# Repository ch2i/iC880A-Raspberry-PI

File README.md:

# Raspberry PI iC880A and LinkLab Lora Gateway Shield

At the begining this shield has been created to help wiring between Raspberry PI and ISMT [iC880A][10] LoraWan concentrator Gateway (SPI version) and to be able to put the whole thing into a outdoor enclosure such as this [one][15].

Then I decided to add some funky stuff like:

**New in V1.2** (tested, working fine)

 - Added push button on GPIO19 to be able to shutdown PI Locally (if you don't use RFM95 with IRQ) 
 - Reversed DHT connector [#4][4]
 - Added FTDI connector to be able to take hand on PI console when in enclosure (lost network or whatever, no more need to get all off the enclosure and connect HDMI cable to see what's going on)
 - Added footprint for excellent Murata OKI-78SR-5 DC/DC 5V
 - Fixed Mini Voltmeter Holes Spacing

**Still V1.1** 

- Footprint for [iC880a][10] ISMT LoraWan concentrator (main goal)
- ~~Can be also used between LinkLabs [board][11] and Raspi~~
- I2C and Grove connectors to be able to add internal/external sensors such as BME280, SI7021 or HTU21D
- Footprint for DC/DC step down if you want to do some simple [POE splitter][16] to power the whole thing thru a network cable or any power 
- Footprint for a simple Lora module such as RFM95 that can be used a Single Channel Gateway or also act as a Lora Node
- Power with DC Barrel connector and terminal block
- Four visual GPIO Led
- Footprint for DHT1x Temperature/Humidity sensors
- Easy to build and solder, 0805 or PTH components
- Holes to fix board on enclosure or other support

# Detailed Description

No specific documentation for now, it's just a kind of wiring helper, please see Gateway section on [TTN Wiki][13] and also on [TTN Forums][14] for more information on these gateways.

You can power the board with 5V going to Raspberry PI USB power directly, in this case use a descent power supply.
You can also use "basic" POE with injector and splitter, this is what I do to oustide (I inject 12V) and use the DC Barrel, in this case I put D4 and a DC/DC Step down calibrated to 5V (**do calibration before beforre pluging any boards/devices because default DC/DC output can be over 5V can fry all your boards**)

If you need to use sensors you can check out these [examples][12], they're just awesome, I'll post examples as soon as I get all working.

If you use linklabs board you can use these [version][2] of packet_forwarder, it has been modified to drive LED of linklabs boards and PPS modem line.

# Installation

No specific documentation for now, it's just a kind of wiring helper, please see Gateway section on [TTN Wiki][13] and Installation is quite easy but as the plate need to go over RPI network and USB connector, you need to use a 2x20 Raspberry PI connector such as [this one][25] form adafruit. You can also find some on ebay.

See generic SX1031 Lora Gateway setup for software [installation](https://github.com/ch2i/LoraGW-Setup)

# Schematic

# Boards 

**Top side**

**Bottom side**

You can order the PCB of this board on my [tindie store](https://www.tindie.com/products/hallard/ic880a-lora-concentrator-shield-raspberry-pi/) located in EU or at [PCBs.io][3] (not sure PCBs.io still alive). Don't worry they still have a bug with top/bottom thumbails view but final boards are okay
PCBs.io give me some reward when you order my designed boards from their site. This is pretty good, because I can use these rewards to create and design new boards and order boards for a discounted price, so if you don't care about PCB manufacturer please use PCBs.io.

## Assembled boards into nice enclosure with sensors

Sensors values en Cayenne (see [installer][26] readme for setup)

## Bill Of Material

Nothing fancy, all components are 0805 and/or PTH and can be ordered almost anywhere (digikey, mouser, radiospare, ...). 
use only what you need dependings on what you want to do. 

- ~~Adjustable DC/DC step down like this [one][18] or this [one][19]~~
- Fixed 5V DC/DC step down like this 3A [one][27] or this 1.5A [one][28] or excellent Murata [OKI-78SR-5][44]
- LED for 4 GPIO (4/23/18/24) are 3mm PTH or 0805, color of your choice
- If you use RFM95, diode for DIO0/DIO1/DIO2 (if you want to use interrupts) are 1N4148 PTH or SOD123
- POE Splitter such as [these][16] and POE injector as this [one][17]
- Terminal blocks are 5MM spacing
- D3 is 1N400x (1N4001, 1N4007, ..) whatever you have, PTH or DO214
- DC/Barell power jack 
- Grove connector and others at [seeedstudio][20]
- ~~Some PI connector with [long pins][21] for pluging this board and Linklabs one~~
- Some 2X20 pins [PI connector][29] for pluging this board  
- Antenna [UFL][22] with [IPEX][23] cable or [SMA][24] if using Lora Module
- Small Enclosure 125x125mm 75mm Height [#1][40] or [#2][41]
- optional [Outdoor protection sleeve][42] for SI7021/HTU21D
- optional [Breakout][43] for enclosure temperature monitoring BME280
- optional tactile switch like this [one][46] or for external on enclosure this [one][47] (connect button LED to Heatbeat LED (GPIO4)
- optional digital [voltmeter][48] to display input voltage
- 2 x [M4 Hex Brass Spacer Standoff][44] to fix board on enclosure, (higher give you more space below to put POE splitter for example) 25mm to 35mm is fine

# License

This work is licensed under a [Creative Commons Attribution-NonCommercial 4.0 International License](http://creativecommons.org/licenses/by-nc/4.0/)    
If you want to do commercial stuff with this project, please contact [CH2i company](https://www.ch2i.eu/en#support) so we can organize an simple agreement.

# Misc

See news and other projects on my [blog][1] 
 
[1]: https://hallard.me
[2]: https://github.com/ch2i/packet_forwarder
[3]: https://PCBs.io/share/rmVdD
[4]: https://github.com/ch2i/iC880A-Raspberry-PI/issues/4

[10]: http://webshop.imst.de/ic880a-spi-lorawan-concentrator-868mhz.html
[11]: http://forum.thethingsnetwork.org/t/raspberry-pi-lorawan-gateway-board/1071
[12]: https://github.com/leon-anavi/rpi-examples
[13]: https://staging.thethingsnetwork.org/wiki/Hardware/Gateways/Overview
[14]: http://forum.thethingsnetwork.org/c/gateways
[15]: https://www.aerial.net/shop/product_info.php?products_id=1102
[16]: https://www.aerial.net/shop/index.php?cPath=22_124
[17]: http://wiki.dragino.com/index.php?title=PoE_Injector
[18]: http://www.ebay.com/itm/2-PCS-MP1584EN-Step-down-Power-DC-DC-3A-Adjustable-Ultra-LM2596-Step-down-Module-/301798394307
[19]: http://www.ebay.com/itm/1x-Tiny-4-5-28V-3A-DC-DC-Buck-Converter-Step-down-Power-Regulator-MP1584EN-/141524007951
[20]: http://www.seeedstudio.com/depot/index.php?main_page=opl_info&opl_id=4
[21]: http://www.ebay.com/itm/170578495165
[22]: http://www.ebay.com/itm/351690376555
[23]: http://www.ebay.com/itm/351738196013
[24]: http://www.ebay.com/itm/371534934746

[25]: https://www.adafruit.com/products/1979
[26]: https://github.com/ch2i/ic880a-gateway/tree/ch2i-rpi-shield

[27]: http://www.ebay.com/itm/121929386506?var=420920026758
[28]: http://www.ebay.com/itm/371348168950
[29]: http://www.ebay.com/itm/351588181858

[30]: https://github.com/ch2i/packet_forwarder/blob/master/poly_pkt_fwd/readme.md

[40]: http://www.ebay.com/itm/262500056078
[41]: http://www.aliexpress.com/item/Free-Shipping-Good-Quality-ABS-Material-Transparent-Cover-IP66-Waterproof-Electrical-Switch-Box-125-125-75mm/32522255056.html
[42]: http://www.aliexpress.com/item/Temperature-and-humidity-Protective-sleeve-Accessories-PCB-for-SHT20-SHT21-SHT25/32695663191.html?spm=2114.13010208.99999999.264.dgLxek
[43]: http://www.ebay.com/itm/401000227934
[44]: http://www.ebay.com/itm/182181715511?var=483966356069
[45]: http://www2.mouser.com/ProductDetail/Murata-Power-Solutions/OKI-78SR-5-15-W36H-C/?qs=sGAEpiMZZMt6Q9lZSPl3Rb6uckMsyldgZf%2f4GdkUxM8%3d
[46]: http://www.ebay.com/itm/391462862706
[47]: http://www.ebay.com/itm/232153789354?var=531358445664
[48]: http://www.ebay.com/itm/301856945402

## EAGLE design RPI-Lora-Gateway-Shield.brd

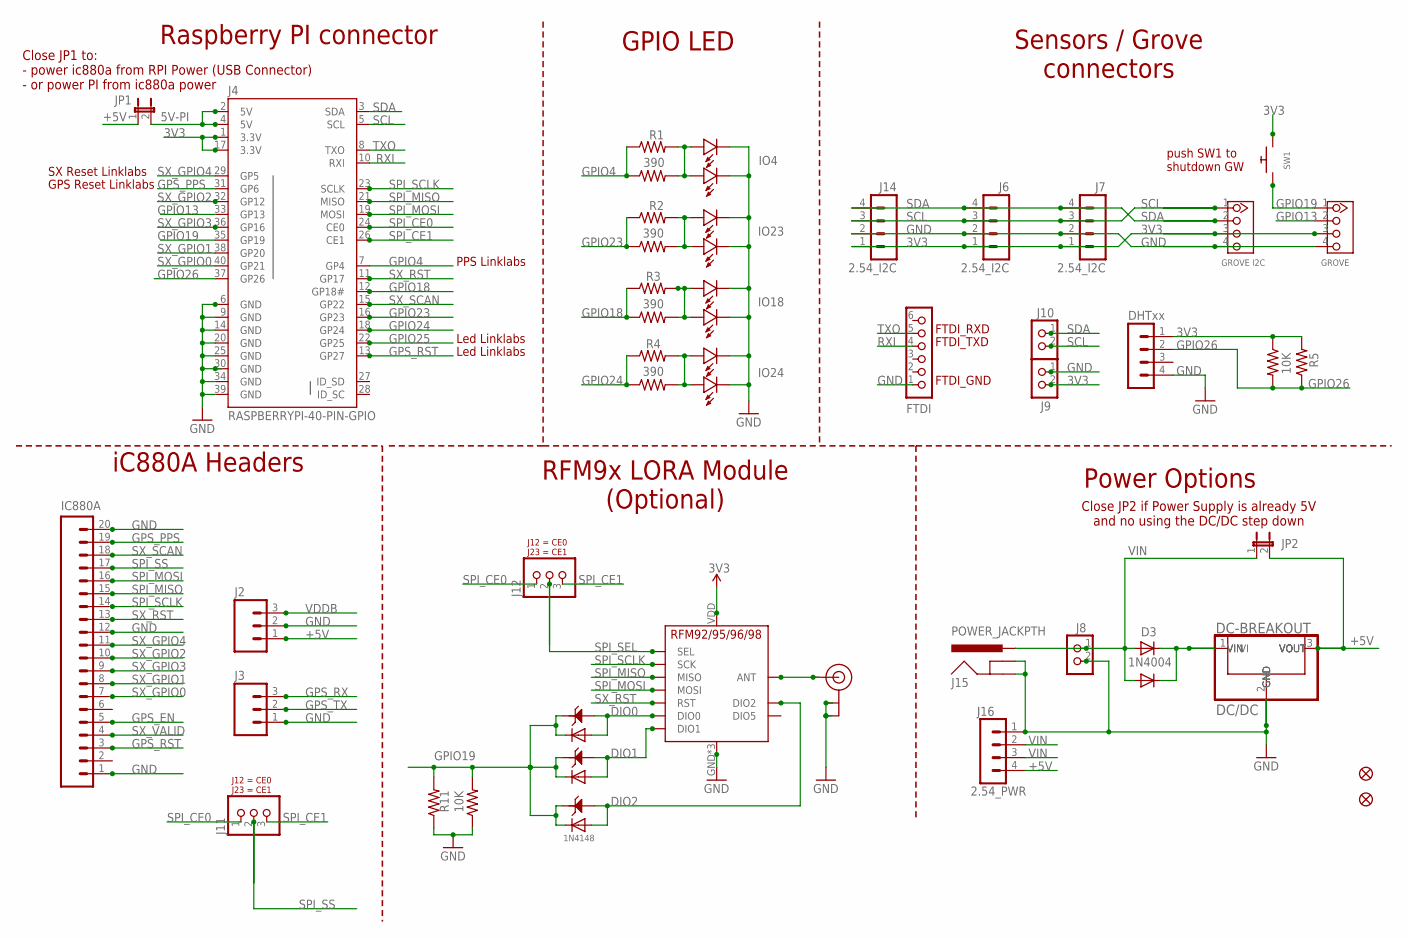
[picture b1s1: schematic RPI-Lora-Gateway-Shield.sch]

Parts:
D0, D1, D2: 1N4148; SOD123-2.7X1.6
D3: 1N4004; DO41-10
D4: 1N4007; DO-214AC
D5: 1N4148; DO-1N4148
D6, D7: DIODEDO-1N4148; DO-1N4148
DC/DC: DC-BREAKOUT
FID2, FID3: FIDUCIAL""; FIDUCIAL_1MM
FTDI: CON_HEADER_1X06-PTH; M1X6
IC880A: M20LOCK; 1X20_LOCK
J1: GROVE; HW4-2.0
J2, J3: M03LOCK; 1X03_LOCK
J4: RASPBERRYPI-40-PIN-GPIO; 2X20-SHROUDED
J5: DHTxx; 1X04_NO_LOCK
J6, J7, J14: 2.54_I2C; 1X04_NO_LOCK
J8, J9, J10: CON_TERMINAL_BLOCK_02-5MM; TERMINAL_BLOCK_2P_5
J11, J12: JUMPER_1X30805; JP3_0805
J13: GROVE I2C; HW4-2.0
J15: POWER_JACKPTH; POWER_JACK_PTH
J16: 2.54_PWR; 1X04_NO_LOCK
JP1, JP2: JUMPER2
LED1, LED2, LED3, LED4: LED0805; 0805-LED
R1, R2, R3, R4: 390; AXIAL-0.4
R5, R11: 10K; AXIAL-0.4
R6, R7, R8, R9, R10, R12: RESISTOR0805-RES; 0805-RES
SW1: SWITCH_PUSHBUTTONEVQ-PE; TACT_PANA-EVQ
U$2: RFM95
U$3: ANTENNA-UFL; UFL_PAD
U$4: IO4; LED3MM
U$5: IO23; LED3MM
U$6: IO18; LED3MM
U$7: IO24; LED3MM
U$8: DC-BREAKOUTFIXED; DC-DC-FIXED
U$11: OKI-78SR; OKI-78SRH

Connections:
3V3: J1.3, J4.1 (3.3V), J4.17 (3.3V), J5.1, J6.1, J7.1, J9.2, J13.3, J14.1, R5.P$1 (1), R10.2, SW1.P$2, U$2.VDD (VCC)
5V-PI: J4.2 (5V), J4.4 (5V), JP1.2
+5V: DC/DC.VOUT-1 (VOUT), DC/DC.VOUT-2 (VOUT), J2.1, J16.4, JP1.1, JP2.2, U$8.VOUT-1 (VOUT), U$8.VOUT-2 (VOUT), U$11.3 (VO)
DIO0: D0.1, D6.A, U$2.DIO0
DIO1: D1.1, D7.A, U$2.DIO1
DIO2: D2.1, D5.A, U$2.DIO2
GND: DC/DC.GND-1 (GND), DC/DC.GND-2 (GND), DC/DC.GND-3 (GND), DC/DC.GND-4 (GND), FTDI.1, IC880A.1, IC880A.12, IC880A.20, J1.4, J2.2, J3.1, J4.6 (GND), J4.9 (GND), J4.14 (GND), J4.20 (GND), J4.25 (GND), J4.30 (GND), J4.34 (GND), J4.39 (GND), J5.4, J6.2, J7.2, J8.2, J9.1, J13.4, J14.2, J15.GND, J15.GNDBREAK, J16.1, LED1.MINUS, LED2.MINUS, LED3.MINUS, LED4.MINUS, R11.P$1 (1), R12.1, U$2.GND, U$2.GND1 (GND), U$2.GND2 (GND), U$3.GND1 (GND), U$3.GND2 (GND), U$4.MINUS, U$5.MINUS, U$6.MINUS, U$7.MINUS, U$8.GND-1 (GND), U$8.GND-2 (GND), U$8.GND-3 (GND), U$8.GND-4 (GND), U$11.2 (GND)
GPIO4: J4.7 (GP4), R1.P$1 (1), R6.1
GPIO13: J1.2, J4.33 (GP13)
GPIO18: J4.12 (GP18#), R3.P$1 (1), R8.1
GPIO19: D0.2, D1.2, D2.2, D5.C, D6.C, D7.C, J1.1, J4.35 (GP19), R11.P$2 (2), R12.2, SW1.P$1
GPIO23: J4.16 (GP23), R2.P$1 (1), R7.1
GPIO24: J4.18 (GP24), R4.P$1 (1), R9.1
GPIO25: J4.22 (GP25)
GPIO26: J4.37 (GP26), J5.2, R5.P$2 (2), R10.1
GPS_EN: IC880A.5
GPS_PPS: IC880A.19, J4.31 (GP6)
GPS_RST: IC880A.3, J4.13 (GP27)
GPS_RX: J3.3
GPS_TX: J3.2
unnamed: D3.C, D4.1 (C), DC/DC.VIN-1 (VIN), DC/DC.VIN-2 (VIN), U$8.VIN-1 (VIN), U$8.VIN-2 (VIN), U$11.1 (VI)
unnamed: LED4.PLUS, R4.P$2 (2), R9.2, U$7.PLUS
unnamed: LED1.PLUS, R1.P$2 (2), R6.2, U$4.PLUS
unnamed: LED2.PLUS, R2.P$2 (2), R7.2, U$5.PLUS
unnamed: LED3.PLUS, R3.P$2 (2), R8.2, U$6.PLUS
unnamed: U$2.ANT, U$3.ANT1 (SIGNAL), U$3.ANT2 (SIGNAL)
RXI: FTDI.4, J4.10 (RXI)
SCL: J4.5 (SCL), J6.3, J7.3, J10.2, J13.1, J14.3
SDA: J4.3 (SDA), J6.4, J7.4, J10.1, J13.2, J14.4
SPI_CE0: J4.24 (CE0), J11.1, J12.1
SPI_CE1: J4.26 (CE1), J11.3, J12.3
SPI_MISO: IC880A.15, J4.21 (MISO), U$2.MISO
SPI_MOSI: IC880A.16, J4.19 (MOSI), U$2.MOSI
SPI_SCLK: IC880A.14, J4.23 (SCLK), U$2.SCK
SPI_SEL: J12.2, U$2.NSS (SEL)
SPI_SS: IC880A.17, J11.2
SX_GPIO0: IC880A.7, J4.40 (GP21)
SX_GPIO1: IC880A.8, J4.38 (GP20)
SX_GPIO2: IC880A.10, J4.32 (GP12)
SX_GPIO3: IC880A.9, J4.36 (GP16)
SX_GPIO4: IC880A.11, J4.29 (GP5)
SX_RST: IC880A.13, J4.11 (GP17), U$2.RST
SX_SCAN: IC880A.18, J4.15 (GP22)
SX_VALID: IC880A.4
TXO: FTDI.5, J4.8 (TXO)
VDDB: J2.3
VIN: D3.A, D4.2 (A), J8.1, J15.PWR, J16.2, J16.3, JP2.1

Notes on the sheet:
PPS Linklabs
SX Reset Linklabs
GPS Reset Linklabs
Led Linklabs
iC880A Headers
RFM9x LORA Module (Optional)
Power Options
Raspberry PI connector
GPIO LED
Sensors / Grove connectors
Close JP2 if Power Supply is already 5V and no using the DC/DC step down
Close JP1 to: - power ic880a from RPI Power (USB Connector) - or power PI from ic880a power
FTDI_RXD
FTDI_TXD
FTDI_GND
push SW1 to shutdown GW

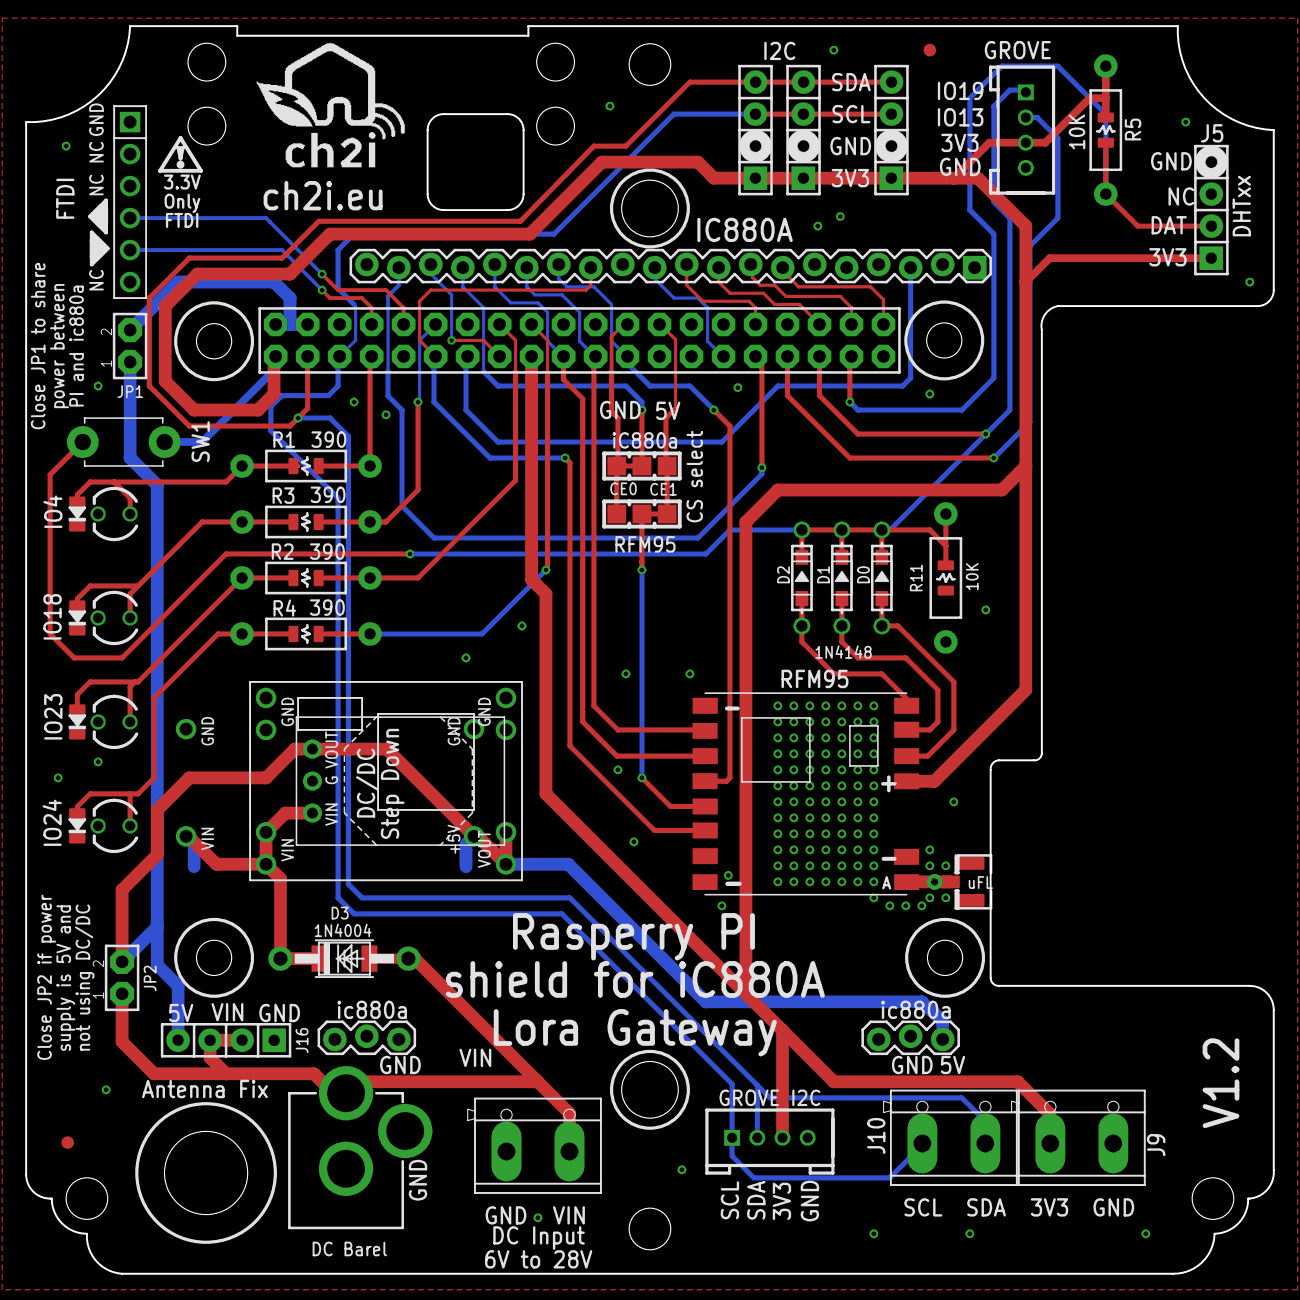
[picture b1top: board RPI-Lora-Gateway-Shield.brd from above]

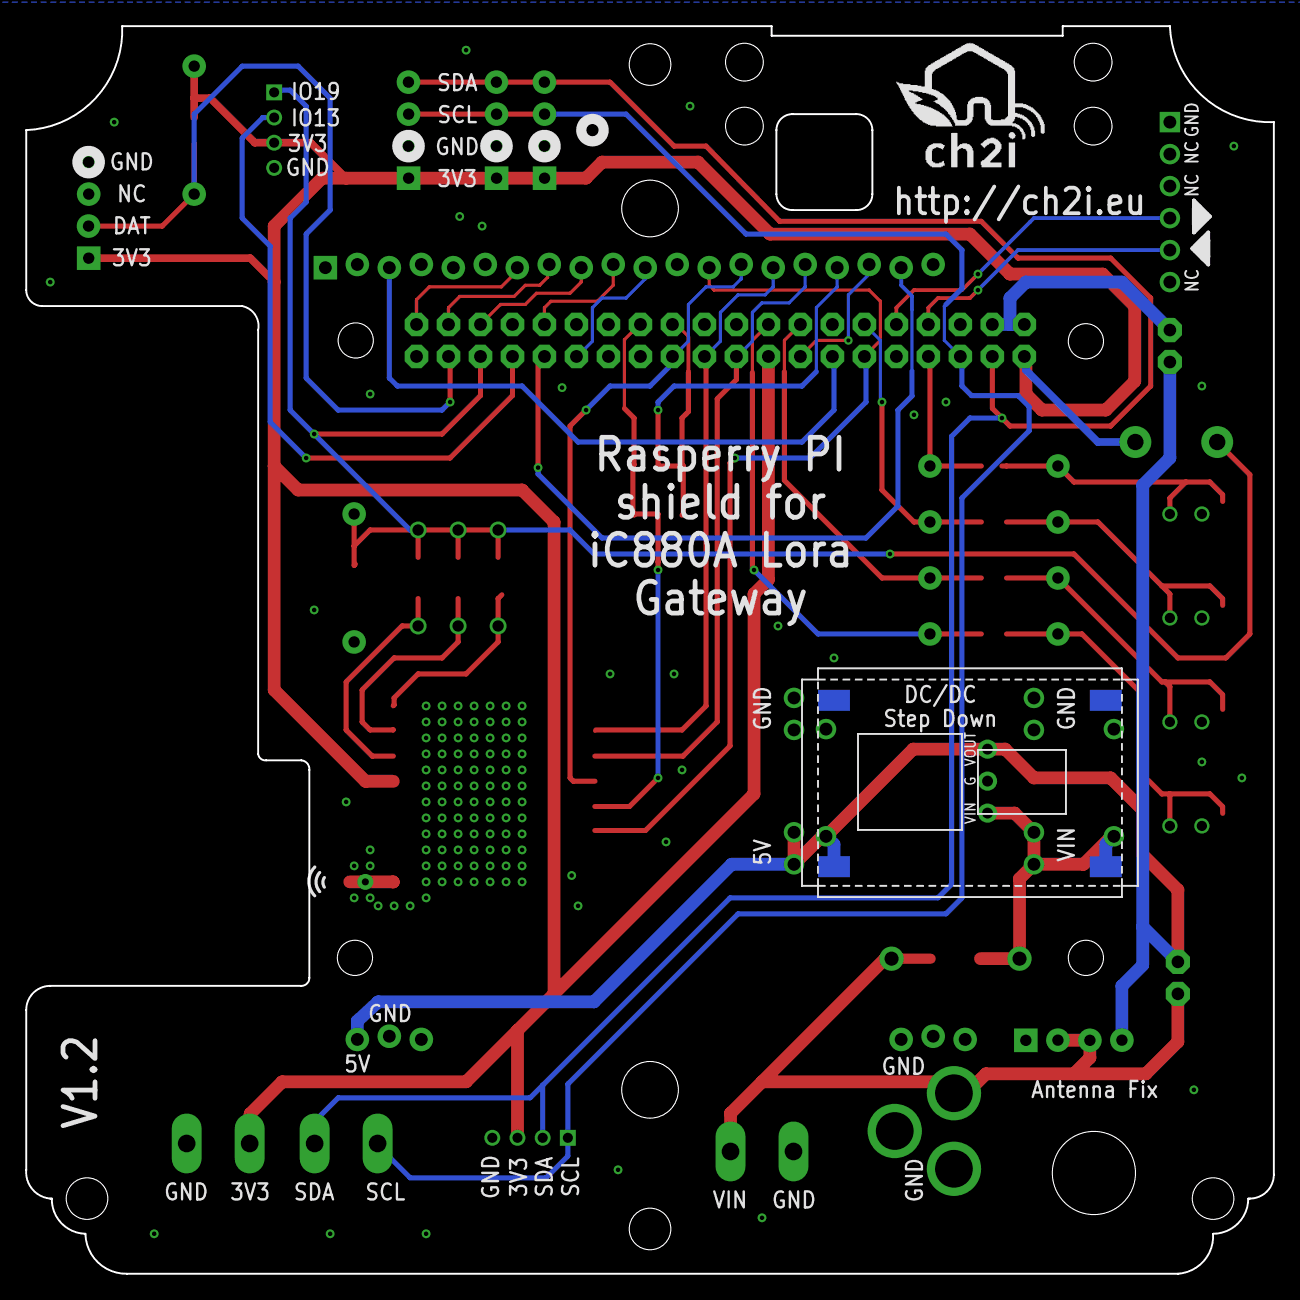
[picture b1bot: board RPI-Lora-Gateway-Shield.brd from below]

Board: 2 copper layers, 99.1 x 99.1 mm, 62 parts (2 on the bottom side), 41 nets.

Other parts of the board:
H1, H2, H3, H4: STAND-OFF
U$1, U$9: LOGO_CH2I_110MM

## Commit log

2016-07-27 :circus_tent: Added .gitattributes
2016-07-27 Creation
2016-07-27 bad links
2016-07-27 bad link
2016-07-27 Minor text changes
2016-07-27 Routing Overlap fix
2016-07-27 Fix routing issue
2016-08-12 Added pictures of final board
2016-08-12 Added documentation and pictures
2016-08-12 Cosmetic
2016-08-12 test title image
2016-09-13 Added link on dedicated poly_packet_forwarder
2016-10-17 Bump to Version 1.1
2016-10-26 Updated License
2016-10-26 Added company link
2016-11-15 bump to V1.1
2016-11-15 Updated BOM and picture for V1.1
2016-11-15 Link updated
2016-11-15 Minor Silk and Trace Fix
2016-11-15 Link update
2016-12-08 Added Picture, Moved installation procedure to installer
2016-12-08 Updated BOM
2016-12-08 Added standoff
2017-06-25 Bump to V1.2
2017-06-25 Cosmetic changes
2017-06-25 Changed DC DC 5V vrong Link
2017-09-18 Added V1.2 pictures and details
2018-03-28 Linked to new installer
2020-10-15 Added Tindie Store
2020-10-15 Tindie Link Fix

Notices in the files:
parts and their libraries:
microbuilder: This work is placed in the public domain, and may be freely used for commercial and non-commercial work with the following conditions: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
SparkFun-Connectors: Licensing: Creative Commons ShareAlike 4.0 International - https://creativecommons.org/licenses/by-sa/4.0
